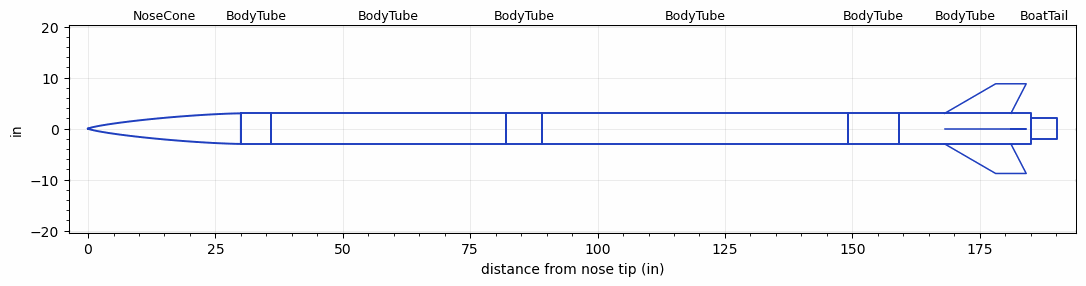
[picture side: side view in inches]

<RASAeroDocument>
 <FileVersion>2</FileVersion>
 <RocketDesign>
  <NoseCone>
   <Length>29.9999</Length>
   <Diameter>6</Diameter>
   <Shape>Von Karman Ogive</Shape>
   <Location>0</Location>
  </NoseCone>
  <BodyTube>
   <Length>6</Length>
   <Diameter>6</Diameter>
   <Location>29.9999</Location>
  </BodyTube>
  <BodyTube>
   <Length>45.9999</Length>
   <Diameter>6</Diameter>
   <Location>35.9999</Location>
  </BodyTube>
  <BodyTube>
   <Length>7.12</Length>
   <Diameter>6</Diameter>
   <Location>81.9998</Location>
  </BodyTube>
  <BodyTube>
   <Length>59.9999</Length>
   <Diameter>6</Diameter>
   <Location>89.1198</Location>
  </BodyTube>
  <BodyTube>
   <Length>10</Length>
   <Diameter>6</Diameter>
   <Location>149.1197</Location>
  </BodyTube>
  <BodyTube>
   <Length>25.9999</Length>
   <Diameter>6</Diameter>
   <Location>159.1197</Location>
   <Fin>
    <Count>4</Count>
    <Chord>13</Chord>
    <Span>5.8</Span>
    <SweepDistance>10</SweepDistance>
    <TipChord>6</TipChord>
    <Thickness>0.3</Thickness>
    <Location>17</Location>
    <AirfoilSection>Subsonic NACA</AirfoilSection>
   </Fin>
  </BodyTube>
  <BoatTail>
   <Length>5</Length>
   <Diameter>4</Diameter>
   <RearDiameter>4</RearDiameter>
   <Location>185.1196</Location>
  </BoatTail>
  <Surface>Rough Camouflage Paint</Surface>
  <CD>0</CD>
  <ModifiedBarrowman>False</ModifiedBarrowman>
  <Turbulence>False</Turbulence>
  <UseBooster1>False</UseBooster1>
  <UseBooster2>False</UseBooster2>
 </RocketDesign>
 <LaunchSite>
  <Altitude>2782.0001</Altitude>
  <Pressure>27.0417</Pressure>
  <RodAngle>0</RodAngle>
  <RodLength>32.8084</RodLength>
  <Temperature>49.0789</Temperature>
  <WindSpeed>4.4739</WindSpeed>
 </LaunchSite>
 <Recovery>
  <Altitude1>1500</Altitude1>
  <Altitude2>656.168</Altitude2>
  <DeviceType1>Parachute</DeviceType1>
  <DeviceType2>Parachute</DeviceType2>
  <Event1>True</Event1>
  <Event2>True</Event2>
  <Size1>143.9997</Size1>
  <Size2>35.9999</Size2>
  <EventType1>Altitude</EventType1>
  <EventType2>Apogee</EventType2>
  <CD1>1.55</CD1>
  <CD2>0</CD2>
 </Recovery>
 <SimulationList>
  <Simulation>
   <SustainerLaunchWt>136.1048</SustainerLaunchWt>
   <SustainerCG>108.1413</SustainerCG>
   <SustainerIgnitionDelay>0</SustainerIgnitionDelay>
   <Booster1SeparationDelay>0</Booster1SeparationDelay>
   <Booster1IgnitionDelay>0</Booster1IgnitionDelay>
   <IncludeBooster1>False</IncludeBooster1>
   <Booster2Delay>0</Booster2Delay>
   <IncludeBooster2>False</IncludeBooster2>
  </Simulation>
  <Simulation>
   <SustainerLaunchWt>136.1048</SustainerLaunchWt>
   <SustainerCG>108.1413</SustainerCG>
   <SustainerIgnitionDelay>0</SustainerIgnitionDelay>
   <Booster1SeparationDelay>0</Booster1SeparationDelay>
   <Booster1IgnitionDelay>0</Booster1IgnitionDelay>
   <IncludeBooster1>False</IncludeBooster1>
   <Booster2Delay>0</Booster2Delay>
   <IncludeBooster2>False</IncludeBooster2>
  </Simulation>
  <Simulation>
   <SustainerLaunchWt>36.1049</SustainerLaunchWt>
   <SustainerCG>77.7342</SustainerCG>
   <SustainerIgnitionDelay>0</SustainerIgnitionDelay>
   <Booster1SeparationDelay>0</Booster1SeparationDelay>
   <Booster1IgnitionDelay>0</Booster1IgnitionDelay>
   <IncludeBooster1>False</IncludeBooster1>
   <Booster2Delay>0</Booster2Delay>
   <IncludeBooster2>False</IncludeBooster2>
  </Simulation>
  <Simulation>
   <SustainerLaunchWt>36.1049</SustainerLaunchWt>
   <SustainerCG>77.7342</SustainerCG>
   <SustainerIgnitionDelay>0</SustainerIgnitionDelay>
   <Booster1SeparationDelay>0</Booster1SeparationDelay>
   <Booster1IgnitionDelay>0</Booster1IgnitionDelay>
   <IncludeBooster1>False</IncludeBooster1>
   <Booster2Delay>0</Booster2Delay>
   <IncludeBooster2>False</IncludeBooster2>
  </Simulation>
  <Simulation>
   <SustainerLaunchWt>36.1049</SustainerLaunchWt>
   <SustainerCG>77.7342</SustainerCG>
   <SustainerIgnitionDelay>0</SustainerIgnitionDelay>
   <Booster1SeparationDelay>0</Booster1SeparationDelay>
   <Booster1IgnitionDelay>0</Booster1IgnitionDelay>
   <IncludeBooster1>False</IncludeBooster1>
   <Booster2Delay>0</Booster2Delay>
   <IncludeBooster2>False</IncludeBooster2>
  </Simulation>
 </SimulationList>
</RASAeroDocument>
